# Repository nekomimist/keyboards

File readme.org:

* Nekomimist's keyboards

** nekonos0 (nekonos prototype)

- Name :: キ1-r0.0 (nakonos0 evt)
- Board :: [[https://e3w2q.github.io/9/][SU120]]を利用した手作り
- Motivation :: 自分の好きなレイアウトを探るためのプロトタイプ
- Firmware :: [[https://github.com/nekomimist/qmk_firmware/tree/nekomimist/keyboards/e3w2q/su120/rev1]]
- Photo :: [[https://twitter.com/nekomimist/status/1332611166024069120][twitter]]

** nekonos1 rev0.1

- Name :: キ1-r0.1 (nekonos1 dvt)
- Board :: 自作
- Board Manufacuter :: Elecrow
- Motivation :: nekonos0を自設計基板で動かすこと
- Firmware :: [[https://github.com/nekomimist/qmk_firmware/tree/nekomimist/keyboards/nkns1/rev01]]
- Photo :: [[https://twitter.com/nekomimist/status/1341686424458805250][twitter]]

** nekonos0r (nekonos prototype-r)

- Name :: キ0-r0.0r (nakonos0r)
- Board :: [[https://e3w2q.github.io/9/][SU120]]を利用した手作り (キ0-r0.0からの一部改造)
- Motivation :: ロータリーエンコーダの使用感確認のため
- Firmware :: [[https://github.com/nekomimist/qmk_firmware/tree/nekomimist/keyboards/e3w2q/su120/rev1_2knob]]
- Photo :: [[https://twitter.com/nekomimist/status/1352829978916704256][twitter]]

** nekonos1 rev0.2

- Name :: キ1-r0.2 (nekonos1)
- Board :: 自作
- Board Manufacuter :: JLCPCB
- Motivation :: ロータリーエンコーダ対応とunderglowとリセットの位置の改善
- Firmware :: [[https://github.com/nekomimist/qmk_firmware/tree/nekomimist/keyboards/nkns1/rev02]]
- Photo :: [[https://twitter.com/nekomimist/status/1358013858917412865][twitter]]

** nekonote0 

- Name :: キ2-r0.0 (nekonote0)
- Board :: [[https://e3w2q.github.io/11/][te96]]を利用した手作り
- Motivation :: 狭ピッチ(18x16mm)一体型Ortholinearキーボードのプロトタイピング
- Firmware :: [[https://github.com/nekomimist/qmk_firmware/tree/nekomimist/keyboards/nknt0]]
- Photo :: [[https://twitter.com/nekomimist/status/1349289225011662850][twitter]]

** nekomacropad0

- Name :: キ3-r0.0 (nekomacropad0)
- Board :: SU120を利用した手作り
- Motivation :: 3Dプリンタを利用して余白ちょっと大き目のケースを試作する
- Motivation :: SU120でProMicroを裏面につけてみる
- Motivation :: remapでキーカスタマイズできるようにする
- Firmware :: https://github.com/nekomimist/qmk_firmware/tree/nekomimist/keyboards/nkmp0
- Case :: いつか整理して上げる
- Photo :: [[https://twitter.com/nekomimist/status/1388371816700284932][twitter]] [[https://twitter.com/nekomimist/status/1388373248652443649][twitter]]

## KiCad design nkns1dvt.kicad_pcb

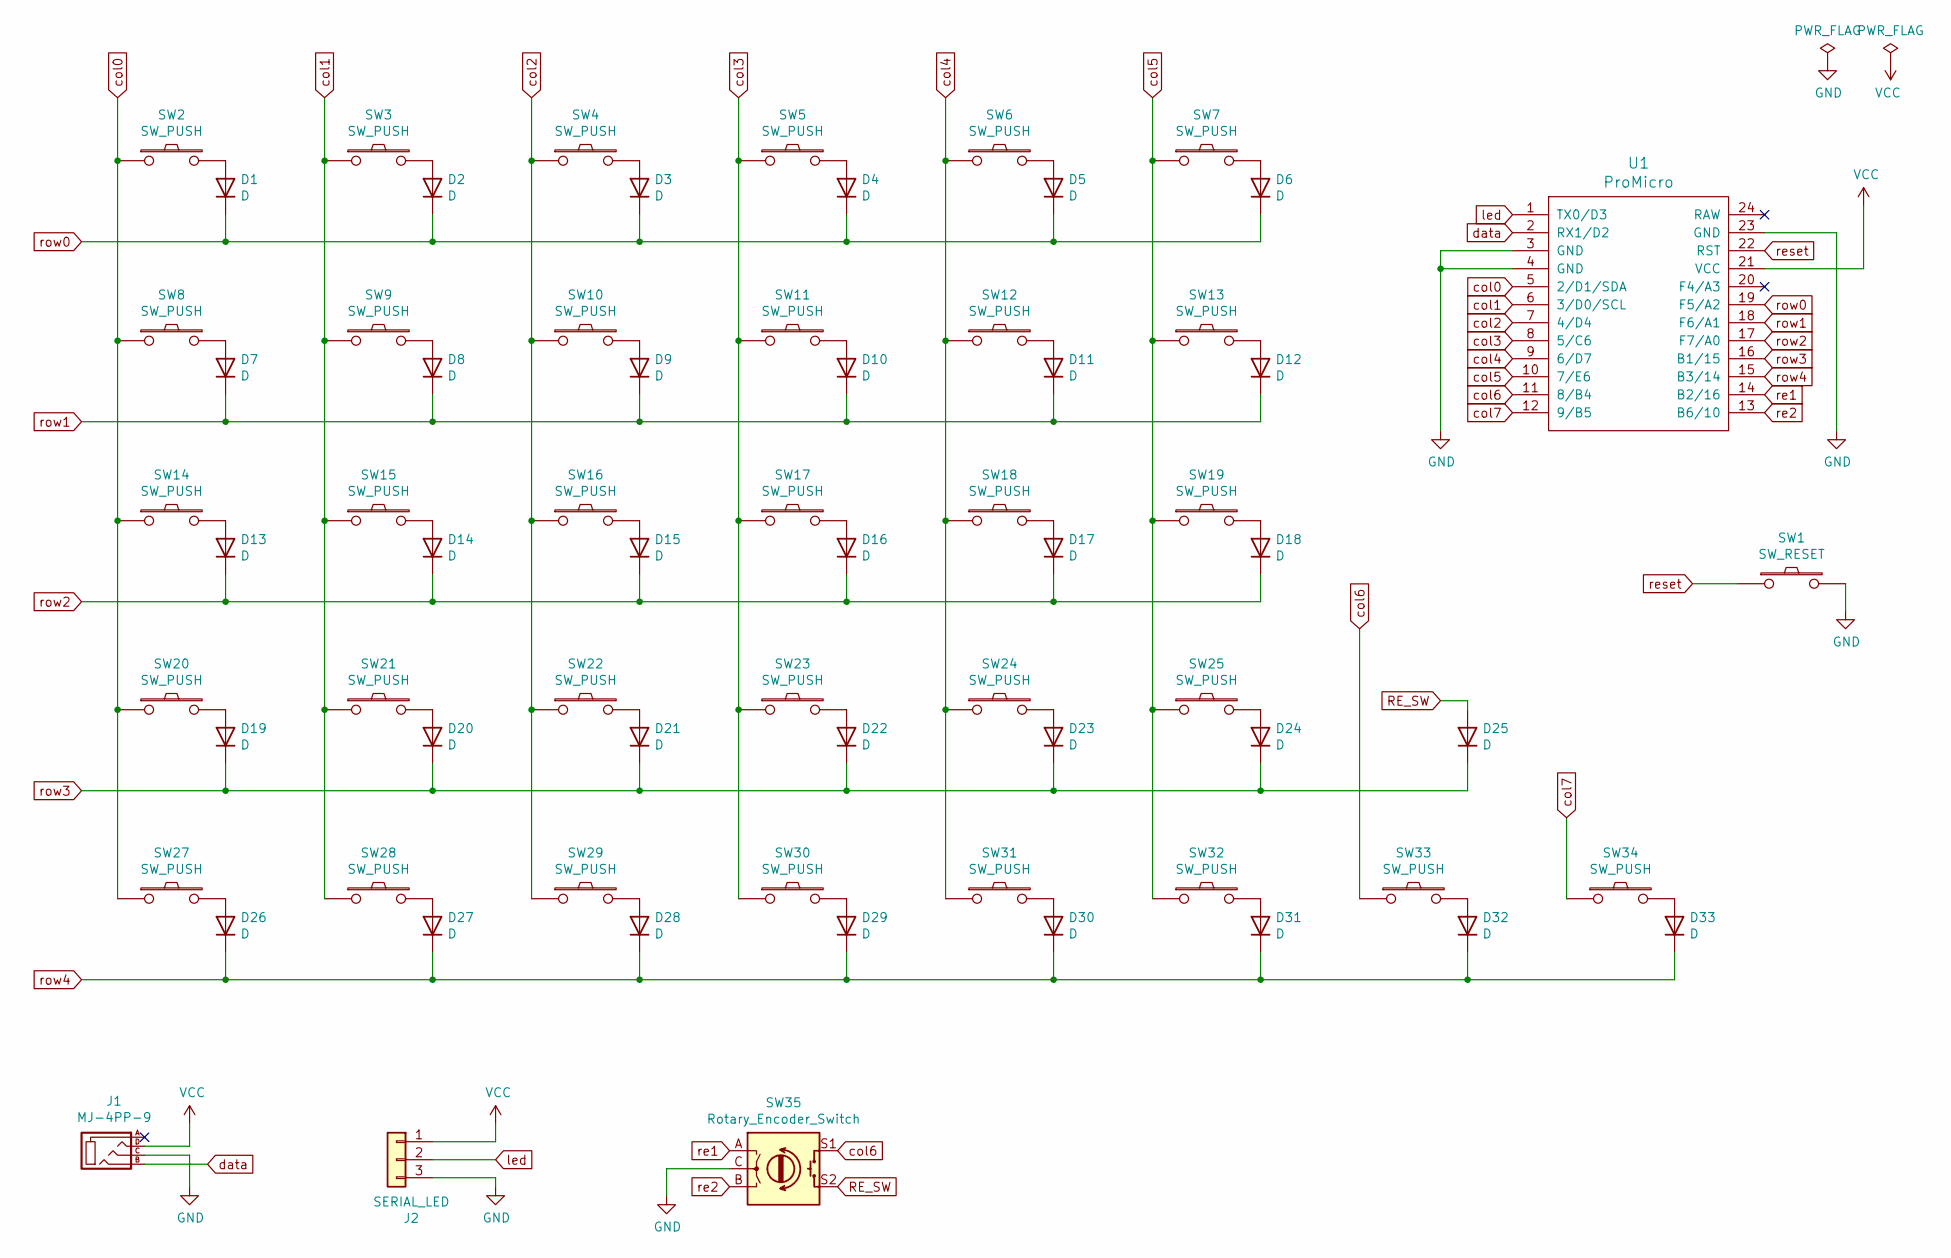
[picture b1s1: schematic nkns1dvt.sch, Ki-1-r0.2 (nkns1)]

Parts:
D1, D2, D3, D4, D5, D6, D7, D8, D9, D10, D11, D12, D13, D14, D15, D16, D17, D18, D19, D20, D21, D22, D23, D24, D25, D26, D27, D28, D29, D30, D31, D32, D33: D; D3_TH_SMD
J1: MJ-4PP-9
J2: SERIAL_LED; StripLED_rev
SW1: SW_RESET; ResetSW
SW2, SW3, SW4, SW5, SW6, SW7, SW8, SW9, SW10, SW11, SW12, SW13, SW14, SW15, SW16, SW17, SW18, SW19, SW20, SW21, SW22, SW23, SW24, SW25, SW27, SW28, SW29, SW30, SW31, SW32, SW33, SW34: SW_PUSH; CherryMX_MidHeight_Hotswap
SW35: Rotary_Encoder_Switch; RotaryEncoder_Alps_EC12E-Switch_Vertical_H20mm
U1: ProMicro; ProMicro_v2

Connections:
GND: J1.C, J2.3, SW1.2, SW35.C, U1.3 (GND), U1.4 (GND), U1.23 (GND)
unnamed: D1.2 (A), SW2.2
unnamed: D2.2 (A), SW3.2
unnamed: D3.2 (A), SW4.2
unnamed: D4.2 (A), SW5.2
unnamed: D5.2 (A), SW6.2
unnamed: D6.2 (A), SW7.2
unnamed: D7.2 (A), SW8.2
unnamed: D8.2 (A), SW9.2
unnamed: D9.2 (A), SW10.2
unnamed: D10.2 (A), SW11.2
unnamed: D11.2 (A), SW12.2
unnamed: D12.2 (A), SW13.2
unnamed: D13.2 (A), SW14.2
unnamed: D14.2 (A), SW15.2
unnamed: D15.2 (A), SW16.2
unnamed: D16.2 (A), SW17.2
unnamed: D17.2 (A), SW18.2
unnamed: D18.2 (A), SW19.2
unnamed: D19.2 (A), SW20.2
unnamed: D20.2 (A), SW21.2
unnamed: D21.2 (A), SW22.2
unnamed: D22.2 (A), SW23.2
unnamed: D23.2 (A), SW24.2
unnamed: D24.2 (A), SW25.2
unnamed: D26.2 (A), SW27.2
unnamed: D27.2 (A), SW28.2
unnamed: D28.2 (A), SW29.2
unnamed: D29.2 (A), SW30.2
unnamed: D30.2 (A), SW31.2
unnamed: D31.2 (A), SW32.2
unnamed: D32.2 (A), SW33.2
unnamed: D33.2 (A), SW34.2
RE_SW: D25.2 (A), SW35.S2
VCC: J1.D, J2.1, U1.21 (VCC)
col0: SW2.1, SW8.1, SW14.1, SW20.1, SW27.1, U1.5 (2/D1/SDA)
col1: SW3.1, SW9.1, SW15.1, SW21.1, SW28.1, U1.6 (3/D0/SCL)
col2: SW4.1, SW10.1, SW16.1, SW22.1, SW29.1, U1.7 (4/D4)
col3: SW5.1, SW11.1, SW17.1, SW23.1, SW30.1, U1.8 (5/C6)
col4: SW6.1, SW12.1, SW18.1, SW24.1, SW31.1, U1.9 (6/D7)
col5: SW7.1, SW13.1, SW19.1, SW25.1, SW32.1, U1.10 (7/E6)
col6: SW33.1, SW35.S1, U1.11 (8/B4)
col7: SW34.1, U1.12 (9/B5)
data: J1.B, U1.2 (RX1/D2)
led: J2.2, U1.1 (TX0/D3)
re1: SW35.A, U1.14 (B2/16)
re2: SW35.B, U1.13 (B6/10)
reset: SW1.1, U1.22 (RST)
row0: D1.1 (K), D2.1 (K), D3.1 (K), D4.1 (K), D5.1 (K), D6.1 (K), U1.19 (F5/A2)
row1: D7.1 (K), D8.1 (K), D9.1 (K), D10.1 (K), D11.1 (K), D12.1 (K), U1.18 (F6/A1)
row2: D13.1 (K), D14.1 (K), D15.1 (K), D16.1 (K), D17.1 (K), D18.1 (K), U1.17 (F7/A0)
row3: D19.1 (K), D20.1 (K), D21.1 (K), D22.1 (K), D23.1 (K), D24.1 (K), D25.1 (K), U1.16 (B1/15)
row4: D26.1 (K), D27.1 (K), D28.1 (K), D29.1 (K), D30.1 (K), D31.1 (K), D32.1 (K), D33.1 (K), U1.15 (B3/14)

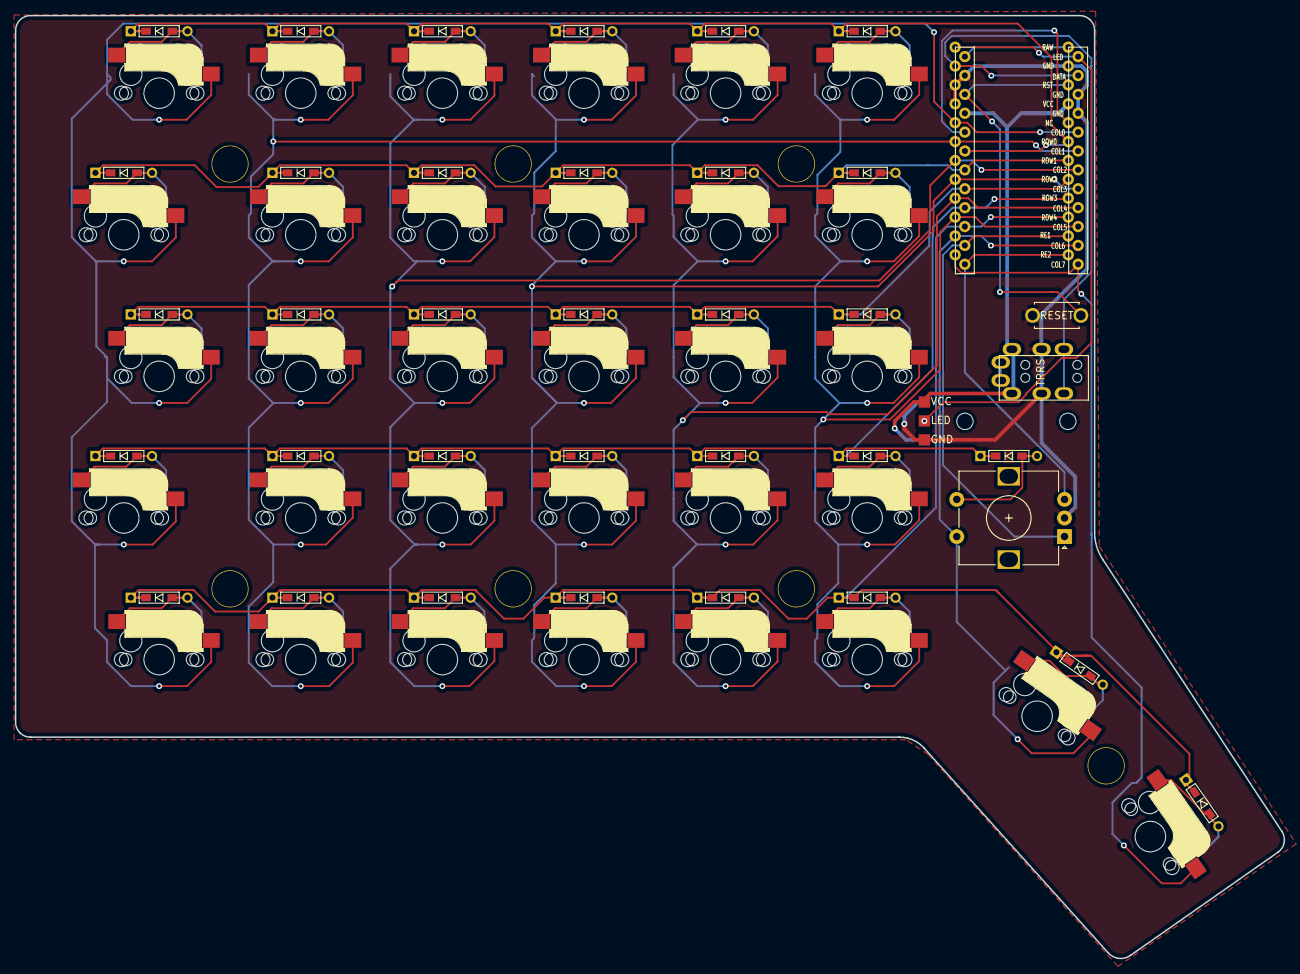
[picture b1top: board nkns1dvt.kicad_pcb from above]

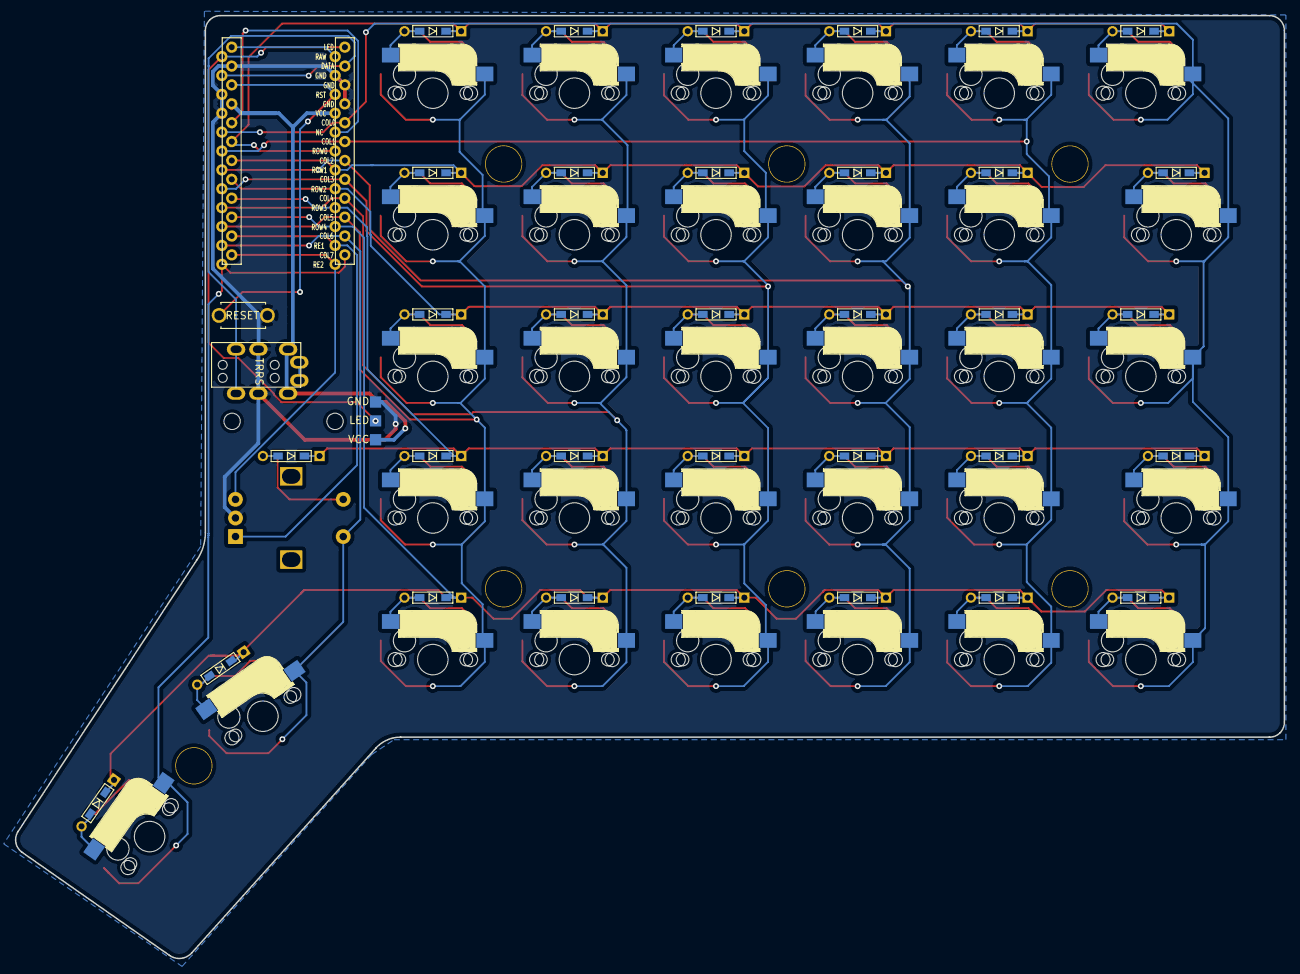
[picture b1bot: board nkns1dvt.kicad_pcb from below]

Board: 2 copper layers, 170.7 x 126.8 mm, 79 parts (2 on the bottom side), 53 nets.

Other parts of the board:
Hole1, Hole2, Hole3, Hole4, Hole5, Hole6, Hole7: HOLE
Hole M1, Hole M2: MountingHole_2.2mm_M2

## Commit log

2020-11-07 Change promicro footprint Change edge layer
2020-11-08 Remove fc-info-cache
2020-11-08 Modify LED. Add GND/VCC route.
2020-11-09 Change to reversible.
2020-11-12 Handwired
2020-11-12 Add wire. Add Mounting hole for ProMicro Area Plate.
2020-11-12 Add beta-GND
2020-11-14 Modify board name.
2020-11-29 Change diode footprints
2020-11-29 Pro Micro横の基板幅を2mmほど小さくした
2020-12-24 nkns1dvt rev.0.1
2021-02-13 nkns1 rev.0.2
    * Change row0-row5 port.
    * Add rotary encoder.
2021-02-13 Modify to plated key holes (nkns1-plate)
2021-02-13 Add plate data for nkns1 r0.1/r0.2
2021-02-13 Modify directory structure
2021-02-13 Add submodules
2021-02-13 Add my footprint library
2021-02-13 Add nekonos prototype & nekonote0's plate data
2021-02-13 Add LICENSE.txt and readme.org
2021-02-13 Fix readme.org
2021-02-13 Rename directory
2021-05-01 Add nkmp0
